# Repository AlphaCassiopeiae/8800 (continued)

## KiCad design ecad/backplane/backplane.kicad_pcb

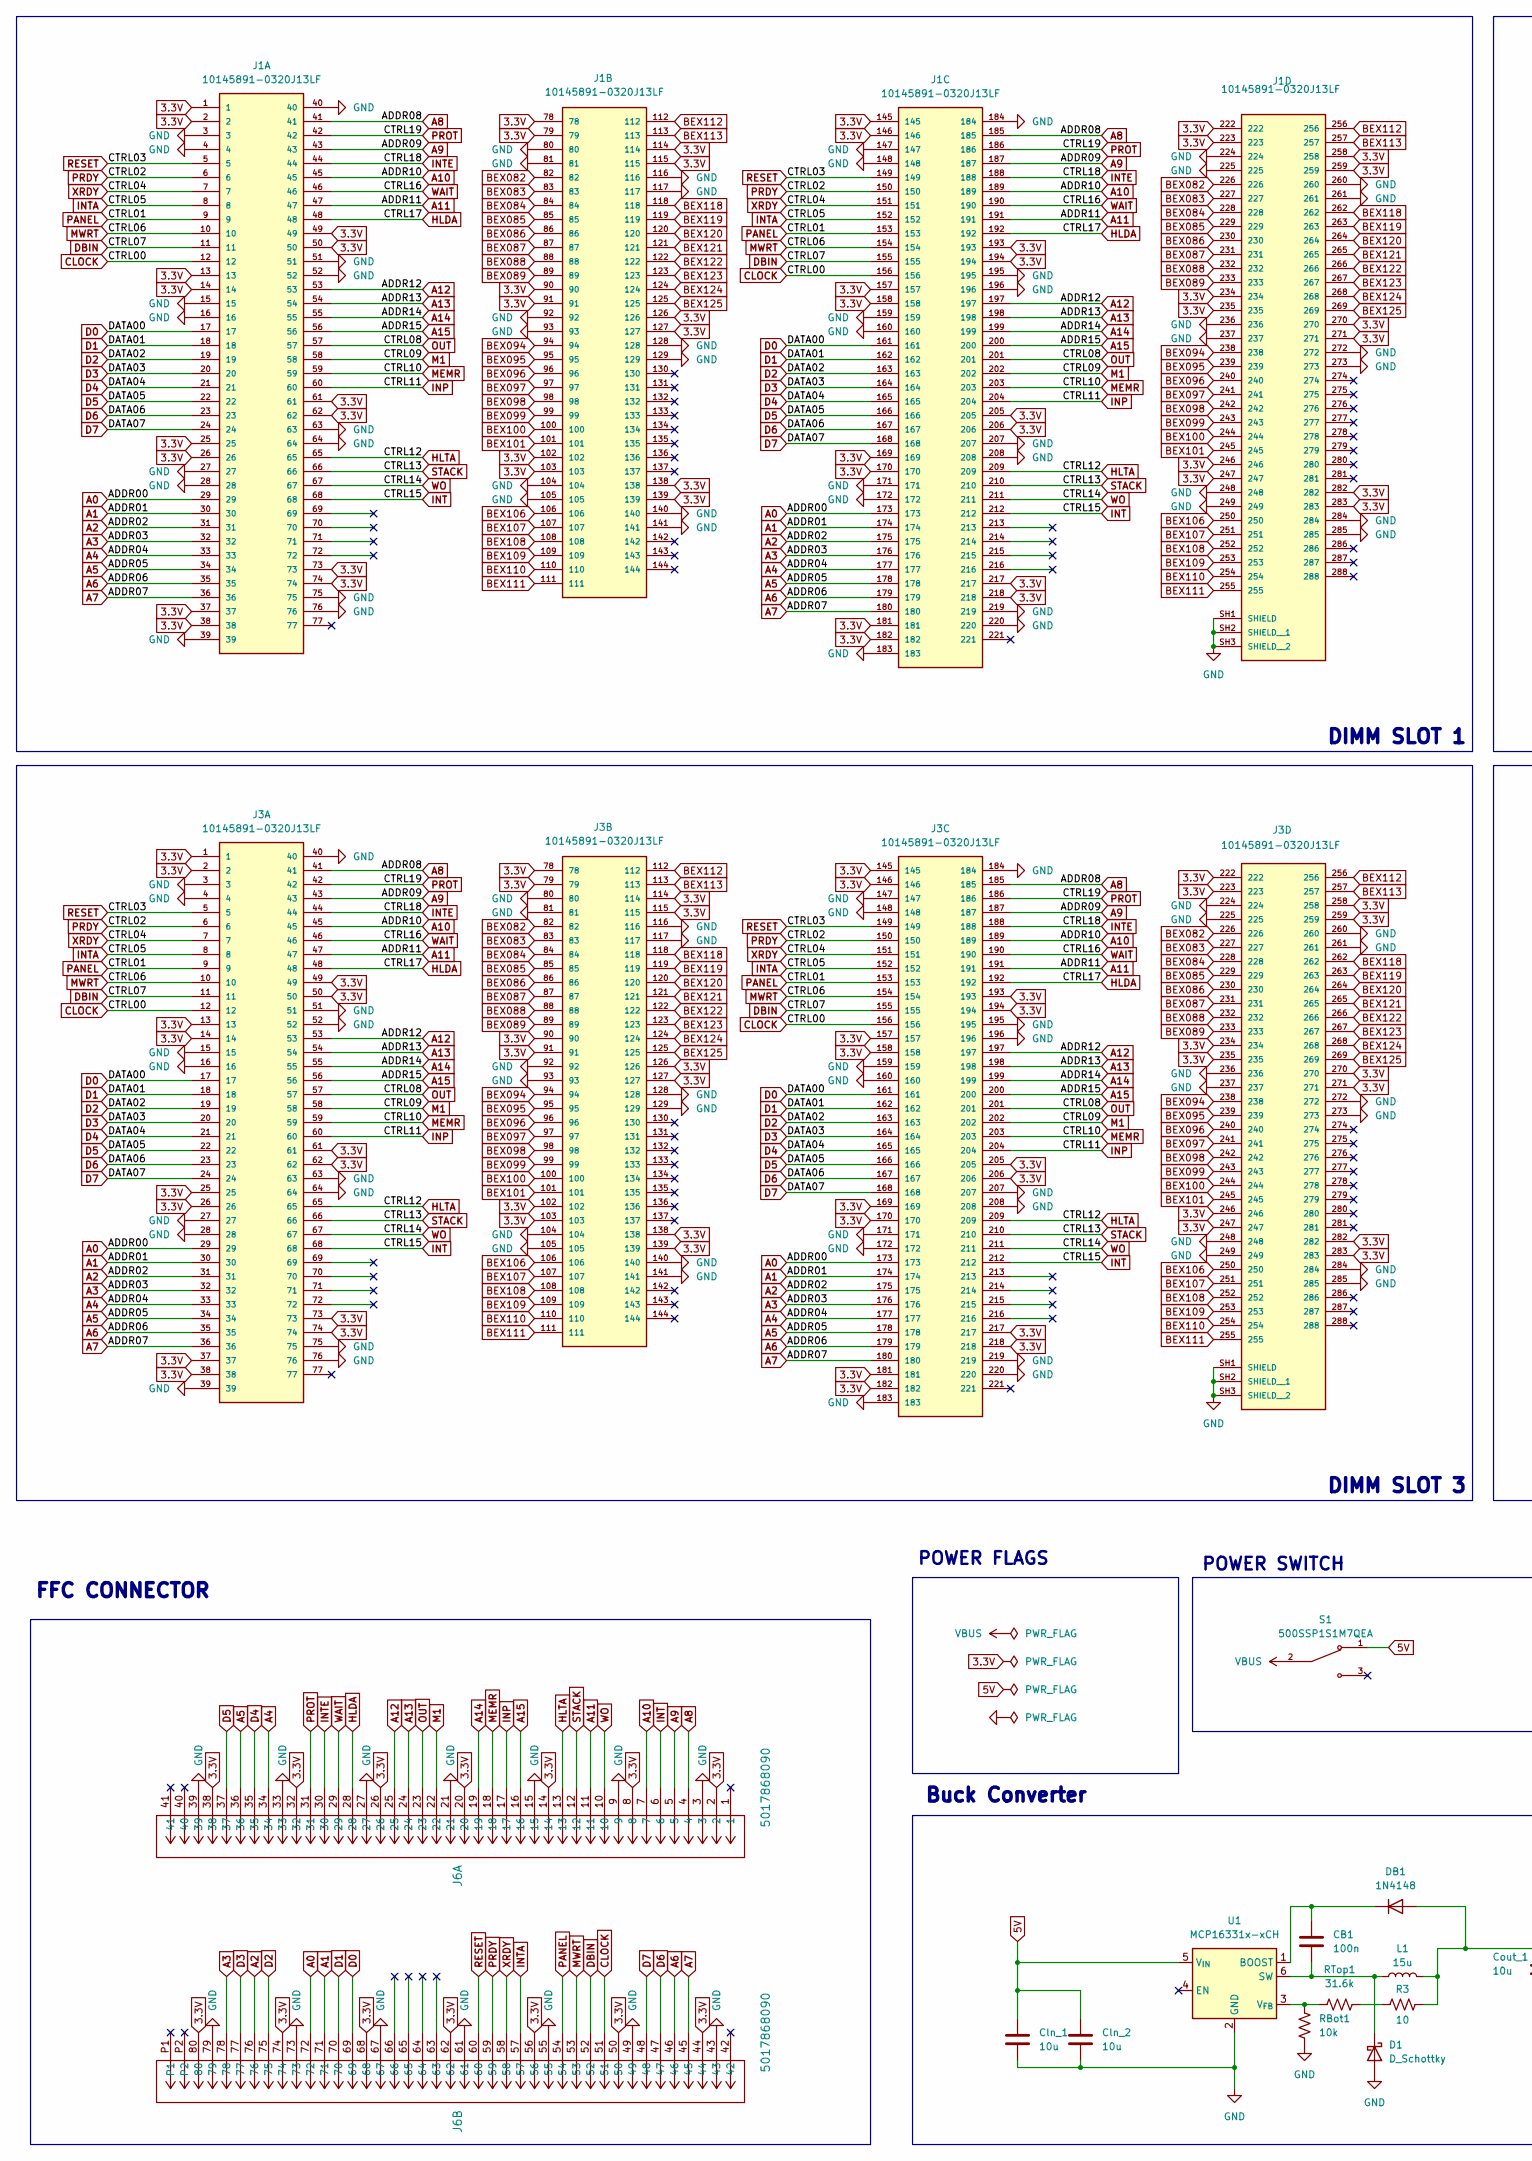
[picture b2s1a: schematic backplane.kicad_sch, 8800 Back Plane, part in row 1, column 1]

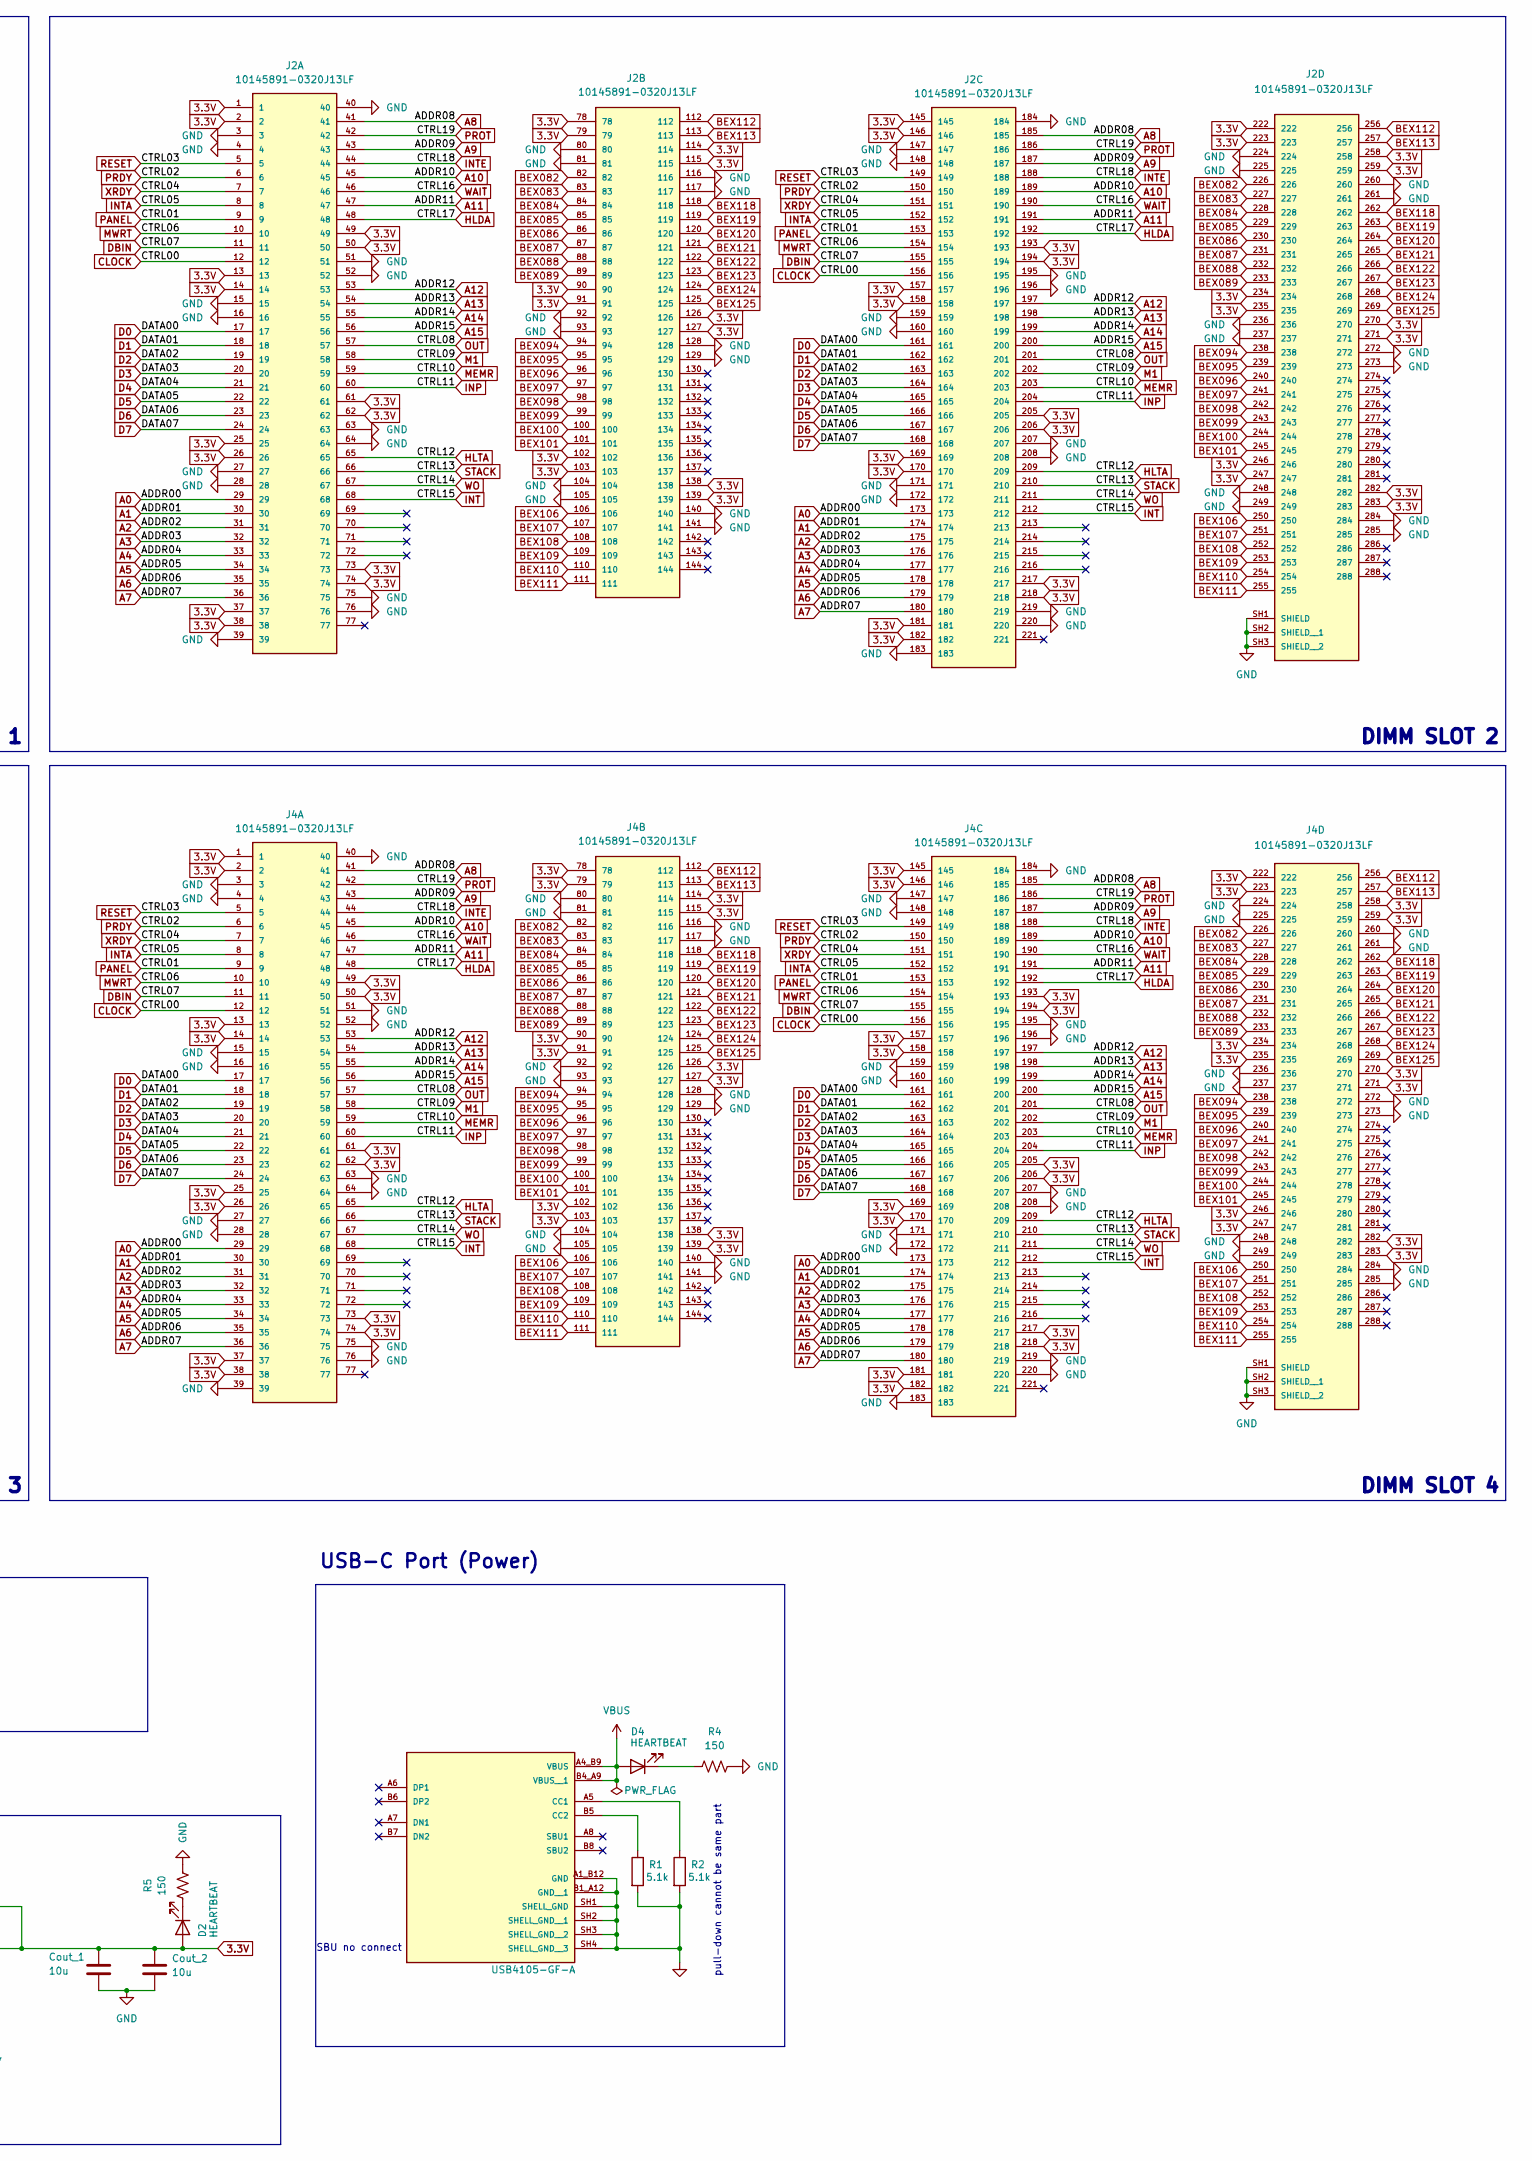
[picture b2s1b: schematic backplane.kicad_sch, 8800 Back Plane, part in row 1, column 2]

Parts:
CB1: 100n; C_0402_1005Metric_Pad0.74x0.62mm_HandSolder
Cln_1, Cln_2: 10u; C_0603_1608Metric_Pad1.08x0.95mm_HandSolder
Cout_1, Cout_2: 10u; C_0402_1005Metric_Pad0.74x0.62mm_HandSolder
D1: D_Schottky; DO-214BA_MCH-L
D2, D4: HEARTBEAT; LED_0603_1608Metric_Pad1.05x0.95mm_HandSolder
DB1: 1N4148; D_0402_1005Metric_Pad0.77x0.64mm_HandSolder
J1, J2, J3, J4: 10145891-0320J13LF; AMPHENOL_10145891-0320J13LF; PARTREV K
J5: USB4105-GF-A; GCT_USB4105-GF-A; PARTREV B4
J6: 5017868090; CON_5017868090
L1: 15u; DR73-150-R
R1, R2: 5.1k; R_0402_1005Metric
R3: 10; R_0402_1005Metric_Pad0.72x0.64mm_HandSolder
R4, R5: 150; R_0402_1005Metric
RBot1: 10k; R_0402_1005Metric_Pad0.72x0.64mm_HandSolder
RTop1: 31.6k; R_0402_1005Metric_Pad0.72x0.64mm_HandSolder
S1: 500SSP1S1M7QEA; SW_500SSP1S1M7QEA; PARTREV 18/10/22
U1: MCP16331x-xCH; SOT-23-6

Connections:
3.3V: Cout_1.1, Cout_2.1, D2.2 (A), DB1.2 (A), J1.1, J1.2, J1.13, J1.14, J1.25, J1.26, J1.37, J1.38, J1.49, J1.50, J1.61, J1.62, J1.73, J1.74, J1.78, J1.79, J1.90, J1.91, J1.102, J1.103, J1.114, J1.115, J1.126, J1.127, J1.138, J1.139, J1.145, J1.146, J1.157, J1.158, J1.169, J1.170, J1.181, J1.182, J1.193, J1.194, J1.205, J1.206, J1.217, J1.218, J1.222, J1.223, J1.234, J1.235, J1.246, J1.247, J1.258, J1.259, J1.270, J1.271, J1.282, J1.283, J2.1, J2.2, J2.13, J2.14, J2.25, J2.26, J2.37, J2.38, J2.49, J2.50, J2.61, J2.62, J2.73, J2.74, J2.78, J2.79, J2.90, J2.91, J2.102, J2.103, J2.114, J2.115, J2.126, J2.127, J2.138, J2.139, J2.145, J2.146, J2.157, J2.158, J2.169, J2.170, J2.181, J2.182, J2.193, J2.194, J2.205, J2.206, J2.217, J2.218, J2.222, J2.223, J2.234, J2.235, J2.246, J2.247, J2.258, J2.259, J2.270, J2.271, J2.282, J2.283, J3.1, J3.2, J3.13, J3.14, J3.25, J3.26, J3.37, J3.38, J3.49, J3.50, J3.61, J3.62, J3.73, J3.74, J3.78, J3.79, J3.90, J3.91, J3.102, J3.103, J3.114, J3.115, J3.126, J3.127, J3.138, J3.139, J3.145, J3.146, J3.157, J3.158, J3.169, J3.170, J3.181, J3.182, J3.193, J3.194, J3.205, J3.206, J3.217, J3.218, J3.222, J3.223, J3.234, J3.235, J3.246, J3.247, J3.258, J3.259, J3.270, J3.271, J3.282, J3.283, J4.1, J4.2, J4.13, J4.14, J4.25, J4.26, J4.37, J4.38, J4.49, J4.50, J4.61, J4.62, J4.73, J4.74, J4.78, J4.79, J4.90, J4.91, J4.102, J4.103, J4.114, J4.115, J4.126, J4.127, J4.138, J4.139, J4.145, J4.146, J4.157, J4.158, J4.169, J4.170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
5V: Cln_1.1, Cln_2.1, S1.1, U1.5 (V_{IN})
A0: J1.29, J1.173, J2.29, J2.173, J3.29, J3.173, J4.29, J4.173, J6.72
A1: J1.30, J1.174, J2.30, J2.174, J3.30, J3.174, J4.30, J4.174, J6.71
A2: J1.31, J1.175, J2.31, J2.175, J3.31, J3.175, J4.31, J4.175, J6.76
A3: J1.32, J1.176, J2.32, J2.176, J3.32, J3.176, J4.32, J4.176, J6.78
A4: J1.33, J1.177, J2.33, J2.177, J3.33, J3.177, J4.33, J4.177, J6.34
A5: J1.34, J1.178, J2.34, J2.178, J3.34, J3.178, J4.34, J4.178, J6.36
A6: J1.35, J1.179, J2.35, J2.179, J3.35, J3.179, J4.35, J4.179, J6.46
A7: J1.36, J1.180, J2.36, J2.180, J3.36, J3.180, J4.36, J4.180, J6.45
A8: J1.41, J1.185, J2.41, J2.185, J3.41, J3.185, J4.41, J4.185, J6.4
A9: J1.43, J1.187, J2.43, J2.187, J3.43, J3.187, J4.43, J4.187, J6.5
A10: J1.45, J1.189, J2.45, J2.189, J3.45, J3.189, J4.45, J4.189, J6.7
A11: J1.47, J1.191, J2.47, J2.191, J3.47, J3.191, J4.47, J4.191, J6.11
A12: J1.53, J1.197, J2.53, J2.197, J3.53, J3.197, J4.53, J4.197, J6.25
A13: J1.54, J1.198, J2.54, J2.198, J3.54, J3.198, J4.54, J4.198, J6.24
A14: J1.55, J1.199, J2.55, J2.199, J3.55, J3.199, J4.55, J4.199, J6.19
A15: J1.56, J1.200, J2.56, J2.200, J3.56, J3.200, J4.56, J4.200, J6.16
BEX082: J1.82, J1.226, J2.82, J2.226, J3.82, J3.226, J4.82, J4.226
BEX083: J1.83, J1.227, J2.83, J2.227, J3.83, J3.227, J4.83, J4.227
BEX084: J1.84, J1.228, J2.84, J2.228, J3.84, J3.228, J4.84, J4.228
BEX085: J1.85, J1.229, J2.85, J2.229, J3.85, J3.229, J4.85, J4.229
BEX086: J1.86, J1.230, J2.86, J2.230, J3.86, J3.230, J4.86, J4.230
BEX087: J1.87, J1.231, J2.87, J2.231, J3.87, J3.231, J4.87, J4.231
BEX088: J1.88, J1.232, J2.88, J2.232, J3.88, J3.232, J4.88, J4.232
BEX089: J1.89, J1.233, J2.89, J2.233, J3.89, J3.233, J4.89, J4.233
BEX094: J1.94, J1.238, J2.94, J2.238, J3.94, J3.238, J4.94, J4.238
BEX095: J1.95, J1.239, J2.95, J2.239, J3.95, J3.239, J4.95, J4.239
BEX096: J1.96, J1.240, J2.96, J2.240, J3.96, J3.240, J4.96, J4.240
BEX097: J1.97, J1.241, J2.97, J2.241, J3.97, J3.241, J4.97, J4.241
BEX098: J1.98, J1.242, J2.98, J2.242, J3.98, J3.242, J4.98, J4.242
BEX099: J1.99, J1.243, J2.99, J2.243, J3.99, J3.243, J4.99, J4.243
BEX100: J1.100, J1.244, J2.100, J2.244, J3.100, J3.244, J4.100, J4.244
BEX101: J1.101, J1.245, J2.101, J2.245, J3.101, J3.245, J4.101, J4.245
BEX106: J1.106, J1.250, J2.106, J2.250, J3.106, J3.250, J4.106, J4.250
BEX107: J1.107, J1.251, J2.107, J2.251, J3.107, J3.251, J4.107, J4.251
BEX108: J1.108, J1.252, J2.108, J2.252, J3.108, J3.252, J4.108, J4.252
BEX109: J1.109, J1.253, J2.109, J2.253, J3.109, J3.253, J4.109, J4.253
BEX110: J1.110, J1.254, J2.110, J2.254, J3.110, J3.254, J4.110, J4.254
BEX111: J1.111, J1.255, J2.111, J2.255, J3.111, J3.255, J4.111, J4.255
BEX112: J1.112, J1.256, J2.112, J2.256, J3.112, J3.256, J4.112, J4.256
BEX113: J1.113, J1.257, J2.113, J2.257, J3.113, J3.257, J4.113, J4.257
BEX118: J1.118, J1.262, J2.118, J2.262, J3.118, J3.262, J4.118, J4.262
BEX119: J1.119, J1.263, J2.119, J2.263, J3.119, J3.263, J4.119, J4.263
BEX120: J1.120, J1.264, J2.120, J2.264, J3.120, J3.264, J4.120, J4.264
BEX121: J1.121, J1.265, J2.121, J2.265, J3.121, J3.265, J4.121, J4.265
BEX122: J1.122, J1.266, J2.122, J2.266, J3.122, J3.266, J4.122, J4.266
BEX123: J1.123, J1.267, J2.123, J2.267, J3.123, J3.267, J4.123, J4.267
BEX124: J1.124, J1.268, J2.124, J2.268, J3.124, J3.268, J4.124, J4.268
BEX125: J1.125, J1.269, J2.125, J2.269, J3.125, J3.269, J4.125, J4.269
CLOCK: J1.12, J1.156, J2.12, J2.156, J3.12, J3.156, J4.12, J4.156, J6.51
D0: J1.17, J1.161, J2.17, J2.161, J3.17, J3.161, J4.17, J4.161, J6.69
D1: J1.18, J1.162, J2.18, J2.162, J3.18, J3.162, J4.18, J4.162, J6.70
D2: J1.19, J1.163, J2.19, J2.163, J3.19, J3.163, J4.19, J4.163, J6.75
D3: J1.20, J1.164, J2.20, J2.164, J3.20, J3.164, J4.20, J4.164, J6.77
D4: J1.21, J1.165, J2.21, J2.165, J3.21, J3.165, J4.21, J4.165, J6.35
D5: J1.22, J1.166, J2.22, J2.166, J3.22, J3.166, J4.22, J4.166, J6.37
D6: J1.23, J1.167, J2.23, J2.167, J3.23, J3.167, J4.23, J4.167, J6.47
D7: J1.24, J1.168, J2.24, J2.168, J3.24, J3.168, J4.24, J4.168, J6.48
DBIN: J1.11, J1.155, J2.11, J2.155, J3.11, J3.155, J4.11, J4.155, J6.52
GND: Cln_1.2, Cln_2.2, Cout_1.2, Cout_2.2, D1.2 (A), J1.3, J1.4, J1.15, J1.16, J1.27, J1.28, J1.39, J1.40, J1.51, J1.52, J1.63, J1.64, J1.75, J1.76, J1.80, J1.81, J1.92, J1.93, J1.104, J1.105, J1.116, J1.117, J1.128, J1.129, J1.140, J1.141, J1.147, J1.148, J1.159, J1.160, J1.171, J1.172, J1.183, J1.184, J1.195, J1.196, J1.207, J1.208, J1.219, J1.220, J1.224, J1.225, J1.236, J1.237, J1.248, J1.249, J1.260, J1.261, J1.272, J1.273, J1.284, J1.285, J1.SH1 (SHIELD), J1.SH2 (SHIELD__1), J1.SH3 (SHIELD__2), J2.3, J2.4, J2.15, J2.16, J2.27, J2.28, J2.39, J2.40, J2.51, J2.52, J2.63, J2.64, J2.75, J2.76, J2.80, J2.81, J2.92, J2.93, J2.104, J2.105, J2.116, J2.117, J2.128, J2.129, J2.140, J2.141, J2.147, J2.148, J2.159, J2.160, J2.171, J2.172, J2.183, J2.184, J2.195, J2.196, J2.207, J2.208, J2.219, J2.220, J2.224, J2.225, J2.236, J2.237, J2.248, J2.249, J2.260, J2.261, J2.272, J2.273, J2.284, J2.285, J2.SH1 (SHIELD), J2.SH2 (SHIELD__1), J2.SH3 (SHIELD__2), J3.3, J3.4, J3.15, J3.16, J3.27, J3.28, J3.39, J3.40, J3.51, J3.52, J3.63, J3.64, J3.75, J3.76, J3.80, J3.81, J3.92, J3.93, J3.104, J3.105, J3.116, J3.117, J3.128, J3.129, J3.140, J3.141, J3.147, J3.148, J3.159, J3.160, J3.171, J3.172, J3.183, J3.184, J3.195, J3.196, J3.207, J3.208, J3.219, J3.220, J3.224, J3.225, J3.236, J3.237, J3.248, J3.249, J3.260, J3.261, J3.272, J3.273, J3.284, J3.285, J3.SH1 (SHIELD), J3.SH2 (SHIELD__1), J3.SH3 (SHIELD__2), J4.3, J4.4, J4.15, J4.16, J4.27, J4.28, J4.39, J4.40, J4.51, J4.52, J4.63, J4.64, J4.75, J4.76, J4.80, J4.81, J4.92, J4.93, J4.104, J4.105, J4.116, J4.117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
HLDA: J1.48, J1.192, J2.48, J2.192, J3.48, J3.192, J4.48, J4.192, J6.28
HLTA: J1.65, J1.209, J2.65, J2.209, J3.65, J3.209, J4.65, J4.209, J6.13
INP: J1.60, J1.204, J2.60, J2.204, J3.60, J3.204, J4.60, J4.204, J6.17
INT: J1.68, J1.212, J2.68, J2.212, J3.68, J3.212, J4.68, J4.212, J6.6
INTA: J1.8, J1.152, J2.8, J2.152, J3.8, J3.152, J4.8, J4.152, J6.57
INTE: J1.44, J1.188, J2.44, J2.188, J3.44, J3.188, J4.44, J4.188, J6.30
M1: J1.58, J1.202, J2.58, J2.202, J3.58, J3.202, J4.58, J4.202, J6.22
MEMR: J1.59, J1.203, J2.59, J2.203, J3.59, J3.203, J4.59, J4.203, J6.18
MWRT: J1.10, J1.154, J2.10, J2.154, J3.10, J3.154, J4.10, J4.154, J6.53
unnamed: CB1.2, D1.1 (K), L1.1, U1.6 (SW)
unnamed: D2.1 (K), R5.1
unnamed: D4.1 (K), R4.1
unnamed: CB1.1, DB1.1 (K), U1.1 (BOOST)
unnamed: J5.A5 (CC1), R2.1
unnamed: J5.B5 (CC2), R1.1
unnamed: R3.1, RTop1.2
unnamed: RBot1.1, RTop1.1, U1.3 (V_{FB})
OUT: J1.57, J1.201, J2.57, J2.201, J3.57, J3.201, J4.57, J4.201, J6.23
PANEL: J1.9, J1.153, J2.9, J2.153, J3.9, J3.153, J4.9, J4.153, J6.54
PRDY: J1.6, J1.150, J2.6, J2.150, J3.6, J3.150, J4.6, J4.150, J6.59
PROT: J1.42, J1.186, J2.42, J2.186, J3.42, J3.186, J4.42, J4.186, J6.31
RESET: J1.5, J1.149, J2.5, J2.149, J3.5, J3.149, J4.5, J4.149, J6.60
STACK: J1.66, J1.210, J2.66, J2.210, J3.66, J3.210, J4.66, J4.210, J6.12
VBUS: D4.2 (A), J5.A4_B9 (VBUS), J5.B4_A9 (VBUS__1), S1.2
WAIT: J1.46, J1.190, J2.46, J2.190, J3.46, J3.190, J4.46, J4.190, J6.29
WO: J1.67, J1.211, J2.67, J2.211, J3.67, J3.211, J4.67, J4.211, J6.10
XRDY: J1.7, J1.151, J2.7, J2.151, J3.7, J3.151, J4.7, J4.151, J6.58

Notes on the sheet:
Buck Converter
FFC CONNECTOR
USB-C Port (Power)
DIMM SLOT 4
DIMM SLOT 3
SBU no connect
POWER FLAGS
DIMM SLOT 2
pull-down cannot be same part
POWER SWITCH
DIMM SLOT 1

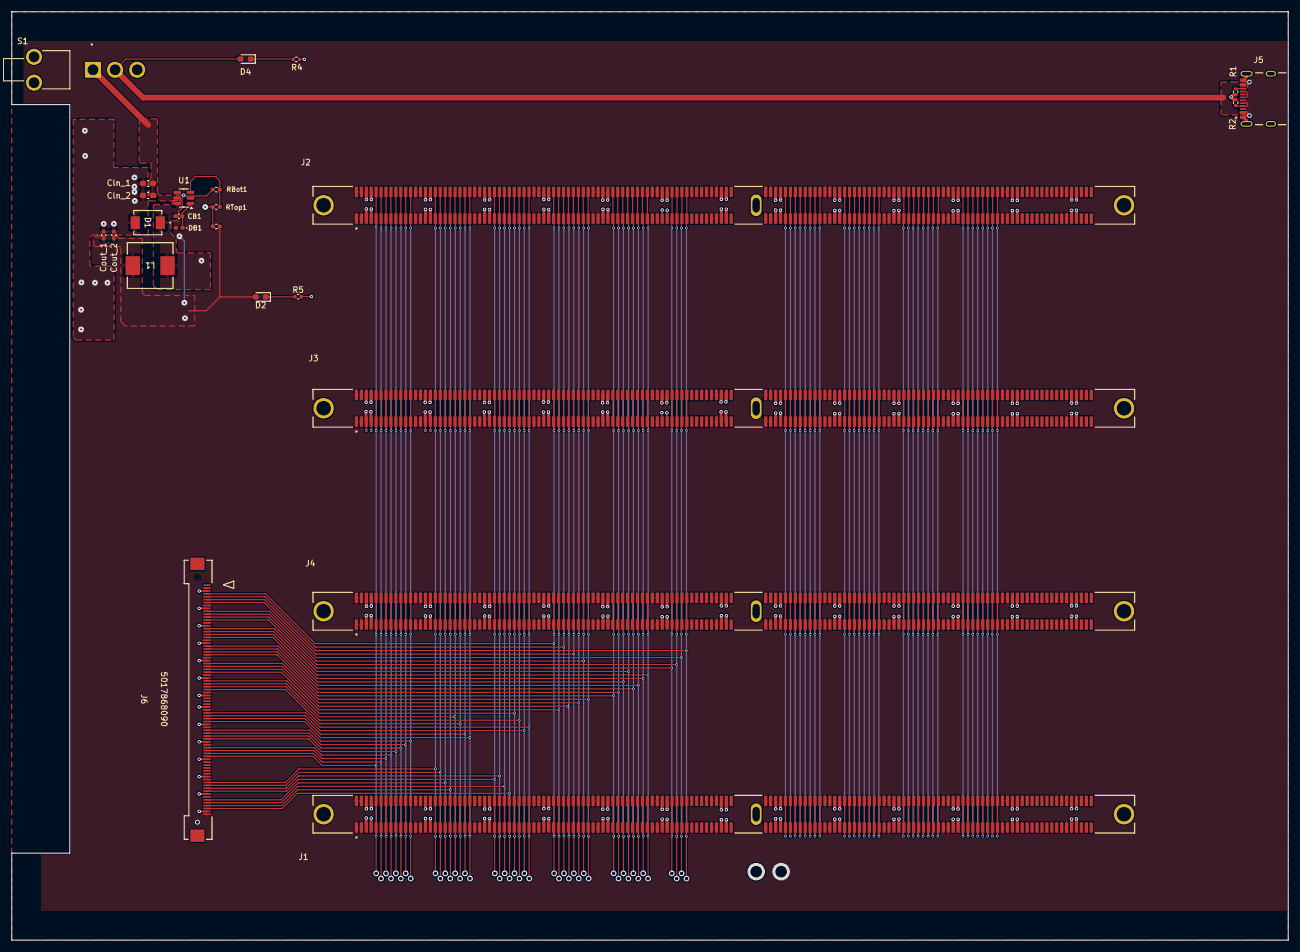
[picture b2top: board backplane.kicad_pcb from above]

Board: 2 copper layers, 220.0 x 160.0 mm, 25 parts (0 on the bottom side), 88 nets.

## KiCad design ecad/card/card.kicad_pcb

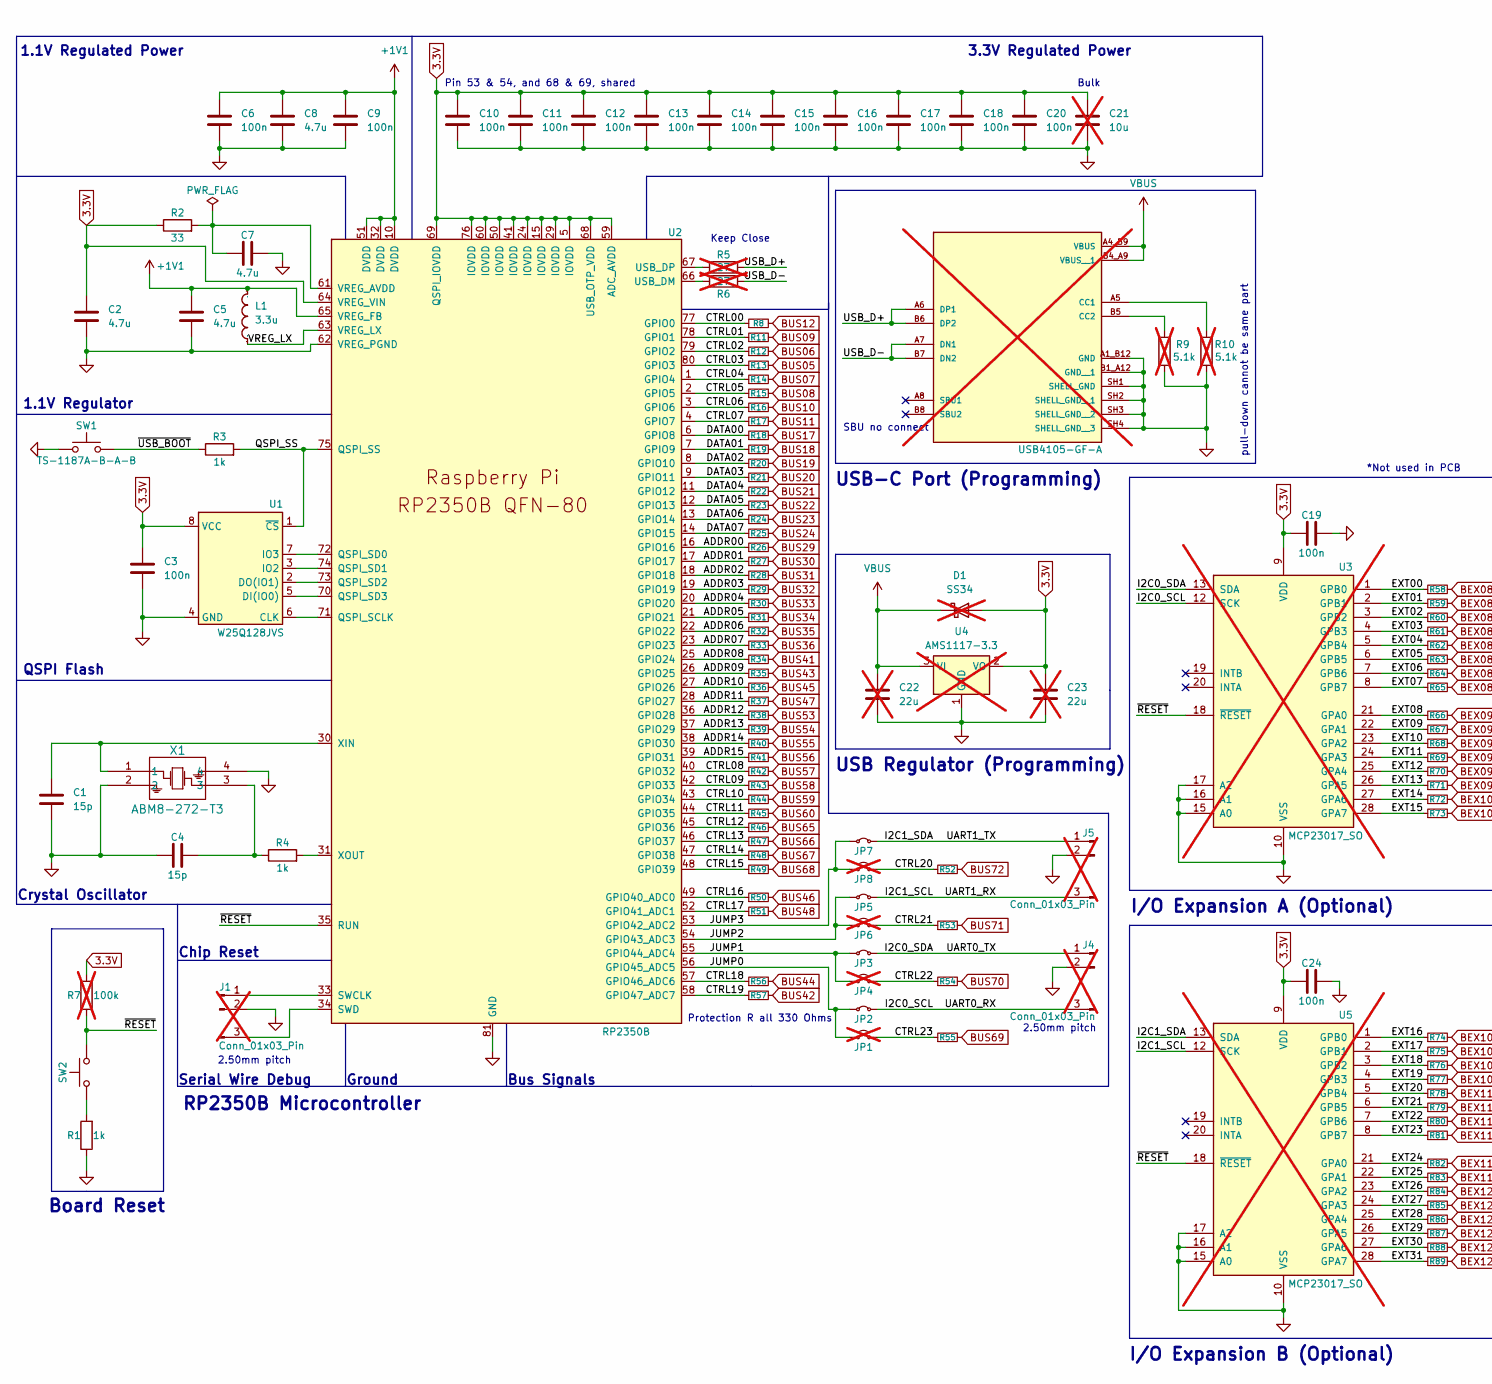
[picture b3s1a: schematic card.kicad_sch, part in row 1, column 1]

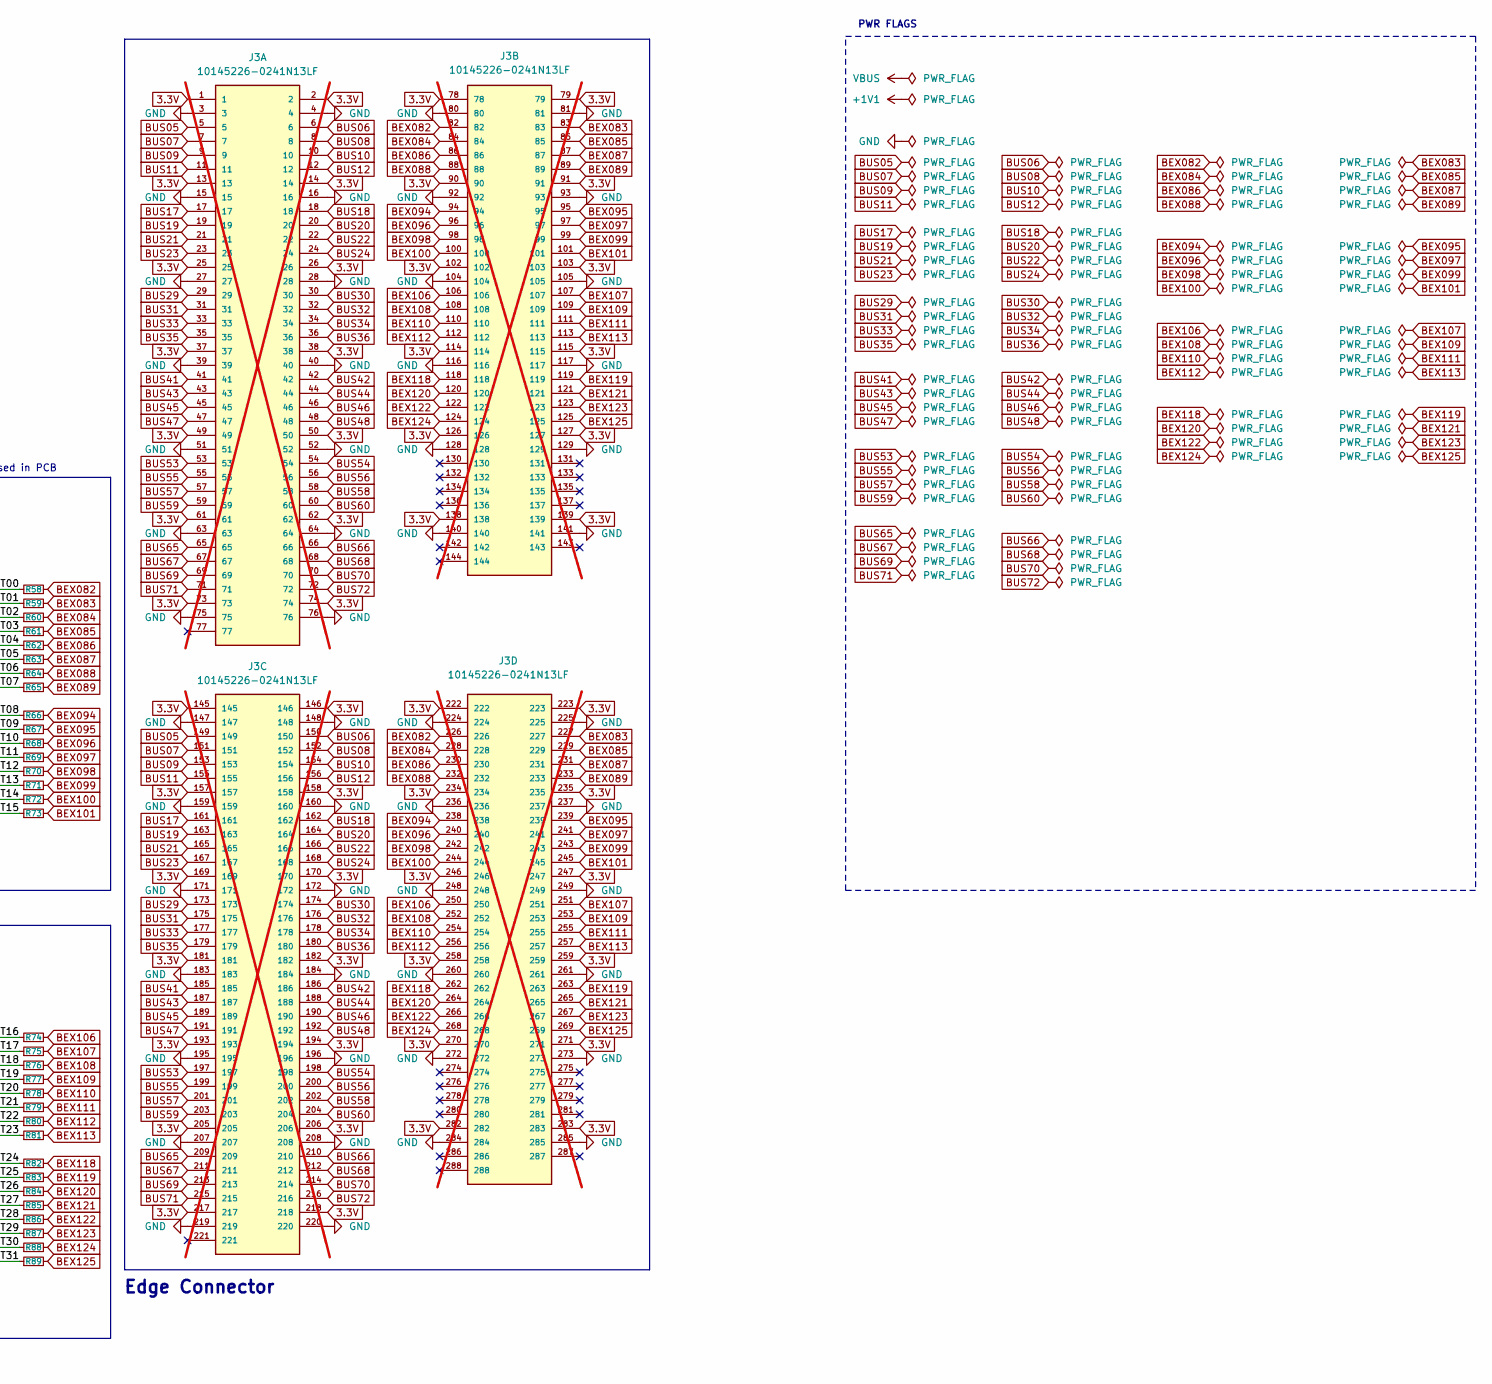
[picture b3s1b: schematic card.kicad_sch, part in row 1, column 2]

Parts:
C1, C4: 15p; C_0402_1005Metric
C2, C7, C8: 4.7u; C_0402_1005Metric
C3, C6, C9, C11, C12, C13, C14, C15, C16, C17, C18, C19, C20, C24: 100n; C_0402_1005Metric
C5: 4.7u; C_0603_1608Metric
C10: 100n; C_0603_1608Metric
C21: 10u; C_0805_2012Metric_Pad1.18x1.45mm_HandSolder; not fitted
C22, C23: 22u; C_1206_3216Metric; not fitted
D1: SS34; D_SMA; not fitted
J1, J4, J5: Conn_01x03_Pin; JST_XH_S3B-XH-A-1_1x03_P2.50mm_Horizontal; not fitted
J2: USB4105-GF-A; GCT_USB4105-GF-A; PARTREV B4; not fitted
J3: 10145226-0241N13LF; DIMM-DDR4; PARTREV E; not fitted
JP1, JP4, JP6, JP8: Jumper_2_Small_Open; R_0402_1005Metric_Pad0.72x0.64mm_HandSolder; not fitted
JP2, JP3, JP5, JP7: 0402WGF0000TCE; R_0402_1005Metric_Pad0.72x0.64mm_HandSolder
L1: 3.3u; IND-SMD_L2.0-W1.6_AOTA-B201610S3R3-101-T; Manufacturer Part AOTA-B201610S3R3-101-T; LCSC Part # C42411119
R1, R3, R4: 1k; R_0402_1005Metric
R2: 33; R_0402_1005Metric
R5, R6: 27; R_0603_1608Metric_Pad0.98x0.95mm_HandSolder; not fitted
R7: 100k; R_0805_2012Metric_Pad1.20x1.40mm_HandSolder; not fitted
R8, R11, R12, R13, R14, R15, R16, R17, R18, R19, R20, R21, R22, R23, R24, R25, R26, R27, R28, R29, R30, R31, R32, R33, R34, R35, R36, R37, R38, R39, R40, R41, R42, R43, R44, R45, R46, R47, R48, R49, R50, R51, R52, R53, R54, R55, R56, R57, R58, R59, R60, R61, R62, R63, R64, R65, R66, R67, R68, R69, R70, R71, R72, R73, R74, R75, R76, R77, R78, R79, R80, R81, R82, R83, R84, R85, R86, R87, R88, R89: 330; R_0402_1005Metric
R9, R10: 5.1k; R_0603_1608Metric_Pad0.98x0.95mm_HandSolder; not fitted
SW1, SW2: TS-1187A-B-A-B; SW_Push_1P1T_XKB_TS-1187A
U1: W25Q128JVS; SOIC-8_5.23x5.23mm_P1.27mm
U2: RP2350B; RP2350-QFN-80-1EP_10x10_P0.4mm_EP3.4x3.4mm_ThermalVias
U3, U5: MCP23017_SO; SOIC-28W_7.5x17.9mm_P1.27mm; not fitted
U4: AMS1117-3.3; SOT-223-3_TabPin2; not fitted
X1: ABM8-272-T3; ABM8-272-T3_ABR

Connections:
3.3V: C2.1, C3.1, C10.1, C11.1, C12.1, C13.1, C14.1, C15.1, C16.1, C17.1, C18.1, C19.1, C20.1, C21.1, C23.1, C24.1, D1.2 (A), J3.1, J3.2, J3.13, J3.14, J3.25, J3.26, J3.37, J3.38, J3.49, J3.50, J3.61, J3.62, J3.73, J3.74, J3.78, J3.79, J3.90, J3.91, J3.102, J3.103, J3.114, J3.115, J3.126, J3.127, J3.138, J3.139, J3.145, J3.146, J3.157, J3.158, J3.169, J3.170, J3.181, J3.182, J3.193, J3.194, J3.205, J3.206, J3.217, J3.218, J3.222, J3.223, J3.234, J3.235, J3.246, J3.247, J3.258, J3.259, J3.270, J3.271, J3.282, J3.283, R2.1, R7.2, U1.8 (VCC), U2.5 (IOVDD), U2.15 (IOVDD), U2.24 (IOVDD), U2.29 (IOVDD), U2.41 (IOVDD), U2.50 (IOVDD), U2.59 (ADC_AVDD), U2.60 (IOVDD), U2.64 (VREG_VIN), U2.68 (USB_OTP_VDD), U2.69 (QSPI_IOVDD), U2.76 (IOVDD), U3.9 (VDD), U4.2 (VO), U5.9 (VDD)
+1V1: C5.1, C6.1, C8.1, C9.1, L1.2, U2.10 (DVDD), U2.32 (DVDD), U2.51 (DVDD), U2.65 (VREG_FB)
/ADDR00: R26.1, U2.16 (GPIO16)
/ADDR01: R27.1, U2.17 (GPIO17)
/ADDR02: R28.1, U2.18 (GPIO18)
/ADDR03: R29.1, U2.19 (GPIO19)
/ADDR04: R30.1, U2.20 (GPIO20)
/ADDR05: R31.1, U2.21 (GPIO21)
/ADDR06: R32.1, U2.22 (GPIO22)
/ADDR07: R33.1, U2.23 (GPIO23)
/ADDR08: R34.1, U2.25 (GPIO24)
/ADDR09: R35.1, U2.26 (GPIO25)
/ADDR10: R36.1, U2.27 (GPIO26)
/ADDR11: R37.1, U2.28 (GPIO27)
/ADDR12: R38.1, U2.36 (GPIO28)
/ADDR13: R39.1, U2.37 (GPIO29)
/ADDR14: R40.1, U2.38 (GPIO30)
/ADDR15: R41.1, U2.39 (GPIO31)
/CTRL00: R8.1, U2.77 (GPIO0)
/CTRL01: R11.1, U2.78 (GPIO1)
/CTRL02: R12.1, U2.79 (GPIO2)
/CTRL03: R13.1, U2.80 (GPIO3)
/CTRL04: R14.1, U2.1 (GPIO4)
/CTRL05: R15.1, U2.2 (GPIO5)
/CTRL06: R16.1, U2.3 (GPIO6)
/CTRL07: R17.1, U2.4 (GPIO7)
/CTRL08: R42.1, U2.40 (GPIO32)
/CTRL09: R43.1, U2.42 (GPIO33)
/CTRL10: R44.1, U2.43 (GPIO34)
/CTRL11: R45.1, U2.44 (GPIO35)
/CTRL12: R46.1, U2.45 (GPIO36)
/CTRL13: R47.1, U2.46 (GPIO37)
/CTRL14: R48.1, U2.47 (GPIO38)
/CTRL15: R49.1, U2.48 (GPIO39)
/CTRL16: R50.1, U2.49 (GPIO40_ADC0)
/CTRL17: R51.1, U2.52 (GPIO41_ADC1)
/CTRL18: R56.1, U2.57 (GPIO46_ADC6)
/CTRL19: R57.1, U2.58 (GPIO47_ADC7)
/CTRL20: JP8.2 (B), R52.1
/CTRL21: JP6.2 (B), R53.1
/CTRL22: JP4.2 (B), R54.1
/CTRL23: JP1.2 (B), R55.1
/DATA00: R18.1, U2.6 (GPIO8)
/DATA01: R19.1, U2.7 (GPIO9)
/DATA02: R20.1, U2.8 (GPIO10)
/DATA03: R21.1, U2.9 (GPIO11)
/DATA04: R22.1, U2.11 (GPIO12)
/DATA05: R23.1, U2.12 (GPIO13)
/DATA06: R24.1, U2.13 (GPIO14)
/DATA07: R25.1, U2.14 (GPIO15)
/EXT00: R58.1, U3.1 (GPB0)
/EXT01: R59.1, U3.2 (GPB1)
/EXT02: R60.1, U3.3 (GPB2)
/EXT03: R61.1, U3.4 (GPB3)
/EXT04: R62.1, U3.5 (GPB4)
/EXT05: R63.1, U3.6 (GPB5)
/EXT06: R64.1, U3.7 (GPB6)
/EXT07: R65.1, U3.8 (GPB7)
/EXT08: R66.1, U3.21 (GPA0)
/EXT09: R67.1, U3.22 (GPA1)
/EXT10: R68.1, U3.23 (GPA2)
/EXT11: R69.1, U3.24 (GPA3)
/EXT12: R70.1, U3.25 (GPA4)
/EXT13: R71.1, U3.26 (GPA5)
/EXT14: R72.1, U3.27 (GPA6)
/EXT15: R73.1, U3.28 (GPA7)
/EXT16: R74.1, U5.1 (GPB0)
/EXT17: R75.1, U5.2 (GPB1)
/EXT18: R76.1, U5.3 (GPB2)
/EXT19: R77.1, U5.4 (GPB3)
/EXT20: R78.1, U5.5 (GPB4)
/EXT21: R79.1, U5.6 (GPB5)
/EXT22: R80.1, U5.7 (GPB6)
/EXT23: R81.1, U5.8 (GPB7)
/EXT24: R82.1, U5.21 (GPA0)
/EXT25: R83.1, U5.22 (GPA1)
/EXT26: R84.1, U5.23 (GPA2)
/EXT27: R85.1, U5.24 (GPA3)
/EXT28: R86.1, U5.25 (GPA4)
/EXT29: R87.1, U5.26 (GPA5)
/EXT30: R88.1, U5.27 (GPA6)
/EXT31: R89.1, U5.28 (GPA7)
/I2C0_SCL: J4.3, JP2.2 (B), U3.12 (SCK)
/I2C0_SDA: J4.1, JP3.2 (B), U3.13 (SDA)
/I2C1_SCL: J5.3, JP5.2 (B), U5.12 (SCK)
/I2C1_SDA: J5.1, JP7.2 (B), U5.13 (SDA)
/JUMP0: JP1.1 (A), JP2.1 (A), U2.56 (GPIO45_ADC5)
/JUMP1: JP3.1 (A), JP4.1 (A), U2.55 (GPIO44_ADC4)
/JUMP2: JP5.1 (A), JP6.1 (A), U2.54 (GPIO43_ADC3)
/JUMP3: JP7.1 (A), JP8.1 (A), U2.53 (GPIO42_ADC2)
/QSPI_SS: R3.2, U1.1 (~CS), U2.75 (QSPI_SS)
/USB_D+: J2.A6 (DP1), J2.B6 (DP2), R5.2
/USB_D-: J2.A7 (DN1), J2.B7 (DN2), R6.1
/VREG_LX: L1.1, U2.63 (VREG_LX)
/~RESET: R7.1, SW2.2, U2.35 (RUN), U3.18 (~RESET), U5.18 (~RESET)
/~USB_BOOT: R3.1, SW1.2
BEX082: J3.82, J3.226, R58.2
BEX083: J3.83, J3.227, R59.2
BEX084: J3.84, J3.228, R60.2
BEX085: J3.85, J3.229, R61.2
BEX086: J3.86, J3.230, R62.2
BEX087: J3.87, J3.231, R63.2
BEX088: J3.88, J3.232, R64.2
BEX089: J3.89, J3.233, R65.2
BEX094: J3.94, J3.238, R66.2
BEX095: J3.95, J3.239, R67.2
BEX096: J3.96, J3.240, R68.2
BEX097: J3.97, J3.241, R69.2
BEX098: J3.98, J3.242, R70.2
BEX099: J3.99, J3.243, R71.2
BEX100: J3.100, J3.244, R72.2
BEX101: J3.101, J3.245, R73.2
BEX106: J3.106, J3.250, R74.2
BEX107: J3.107, J3.251, R75.2
BEX108: J3.108, J3.252, R76.2
BEX109: J3.109, J3.253, R77.2
BEX110: J3.110, J3.254, R78.2
BEX111: J3.111, J3.255, R79.2
BEX112: J3.112, J3.256, R80.2
BEX113: J3.113, J3.257, R81.2
BEX118: J3.118, J3.262, R82.2
BEX119: J3.119, J3.263, R83.2
BEX120: J3.120, J3.264, R84.2
BEX121: J3.121, J3.265, R85.2
BEX122: J3.122, J3.266, R86.2
BEX123: J3.123, J3.267, R87.2
BEX124: J3.124, J3.268, R88.2
BEX125: J3.125, J3.269, R89.2
BUS05: J3.5, J3.149, R13.2
BUS06: J3.6, J3.150, R12.2
BUS07: J3.7, J3.151, R14.2
BUS08: J3.8, J3.152, R15.2
BUS09: J3.9, J3.153, R11.2
BUS10: J3.10, J3.154, R16.2
BUS11: J3.11, J3.155, R17.2
BUS12: J3.12, J3.156, R8.2
BUS17: J3.17, J3.161, R18.2
BUS18: J3.18, J3.162, R19.2
BUS19: J3.19, J3.163, R20.2
BUS20: J3.20, J3.164, R21.2
BUS21: J3.21, J3.165, R22.2
BUS22: J3.22, J3.166, R23.2
BUS23: J3.23, J3.167, R24.2
BUS24: J3.24, J3.168, R25.2
BUS29: J3.29, J3.173, R26.2
BUS30: J3.30, J3.174, R27.2
BUS31: J3.31, J3.175, R28.2
BUS32: J3.32, J3.176, R29.2
BUS33: J3.33, J3.177, R30.2
BUS34: J3.34, J3.178, R31.2
BUS35: J3.35, J3.179, R32.2
BUS36: J3.36, J3.180, R33.2
BUS41: J3.41, J3.185, R34.2
BUS42: J3.42, J3.186, R57.2
BUS43: J3.43, J3.187, R35.2
BUS44: J3.44, J3.188, R56.2
BUS45: J3.45, J3.189, R36.2
BUS46: J3.46, J3.190, R50.2
BUS47: J3.47, J3.191, R37.2
BUS48: J3.48, J3.192, R51.2
BUS53: J3.53, J3.197, R38.2
BUS54: J3.54, J3.198, R39.2
BUS55: J3.55, J3.199, R40.2
BUS56: J3.56, J3.200, R41.2
BUS57: J3.57, J3.201, R42.2
BUS58: J3.58, J3.202, R43.2
BUS59: J3.59, J3.203, R44.2
BUS60: J3.60, J3.204, R45.2
BUS65: J3.65, J3.209, R46.2
BUS66: J3.66, J3.210, R47.2
BUS67: J3.67, J3.211, R48.2
BUS68: J3.68, J3.212, R49.2
BUS69: J3.69, J3.213, R55.2
BUS70: J3.70, J3.214, R54.2
BUS71: J3.71, J3.215, R53.2
BUS72: J3.72, J3.216, R52.2
GND: C1.2, C2.2, C3.2, C4.1, C5.2, C6.2, C7.2, C8.2, C9.2, C10.2, C11.2, C12.2, C13.2, C14.2, C15.2, C16.2, C17.2, C18.2, C19.2, C20.2, C21.2, C22.2, C23.2, C24.2, J1.2, J2.A1_B12 (GND), J2.B1_A12 (GND__1), J2.SH1 (SHELL_GND), J2.SH2 (SHELL_GND__1), J2.SH3 (SHELL_GND__2), J2.SH4 (SHELL_GND__3), J3.3, J3.4, J3.15, J3.16, J3.27, J3.28, J3.39, J3.40, J3.51, J3.52, J3.63, J3.64, J3.75, J3.76, J3.80, J3.81, J3.92, J3.93, J3.104, J3.105, J3.116, J3.117, J3.128, J3.129, J3.140, J3.141, J3.147, J3.148, J3.159, J3.160, J3.171, J3.172, J3.183, J3.184, J3.195, J3.196, J3.207, J3.208, J3.219, J3.220, J3.224, J3.225, J3.236, J3.237, J3.248, J3.249, J3.260, J3.261, J3.272, J3.273, J3.284, J3.285, J4.2, J5.2, R1.1, R9.2, R10.2, SW1.1, U1.4 (GND), U2.62 (VREG_PGND), U2.81 (GND), U3.10 (VSS), U3.15 (A0), U3.16 (A1), U3.17 (A2), U4.1 (GND), U5.10 (VSS), U5.15 (A0), U5.16 (A1), U5.17 (A2), X1.2, X1.4
unnamed: C4.2, R4.1, X1.3
unnamed: J1.1, U2.33 (SWCLK)
unnamed: J1.3, U2.34 (SWD)
unnamed: J2.A5 (CC1), R10.1
unnamed: J2.B5 (CC2), R9.1
unnamed: R1.2, SW2.1
unnamed: U1.6 (CLK), U2.71 (QSPI_SCLK)
unnamed: U1.5 (DI(IO0)), U2.70 (QSPI_SD3)
unnamed: U1.2 (DO(IO1)), U2.73 (QSPI_SD2)
unnamed: U1.3 (IO2), U2.74 (QSPI_SD1)
unnamed: U1.7 (IO3), U2.72 (QSPI_SD0)
unnamed: R6.2, U2.66 (USB_DM)
unnamed: R5.1, U2.67 (USB_DP)
unnamed: C7.1, R2.2, U2.61 (VREG_AVDD)
unnamed: C1.1, U2.30 (XIN), X1.1
unnamed: R4.2, U2.31 (XOUT)
VBUS: C22.1, D1.1 (K), J2.A4_B9 (VBUS), J2.B4_A9 (VBUS__1), U4.3 (VI)

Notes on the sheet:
Crystal Oscillator
Ground
Chip Reset
Protection R all 330 Ohms
SBU no connect
1.1V Regulator
1.1V Regulated Power
2.50mm pitch
I/O Expansion B (Optional)
Bulk
RP2350B Microcontroller
pull-down cannot be same part
Keep Close
USB Regulator (Programming)
QSPI Flash
I/O Expansion A (Optional)
Board Reset
Pin 53 & 54, and 68 & 69, shared
Serial Wire Debug
USB-C Port (Programming)
3.3V Regulated Power
Edge Connector
*Not used in PCB
PWR FLAGS
Bus Signals
